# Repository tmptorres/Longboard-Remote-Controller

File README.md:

# Longboard-Remote-Controller

A remote controller board that uses an Arduino Nano and a 2.4GHz nRF24 WiFi module to send an analog input from a joystic (thumbstick). Power is provided by a 18650 Lithium-ion (Li-ion/Liion) battery.

## Product

## Top View

## Bottom View

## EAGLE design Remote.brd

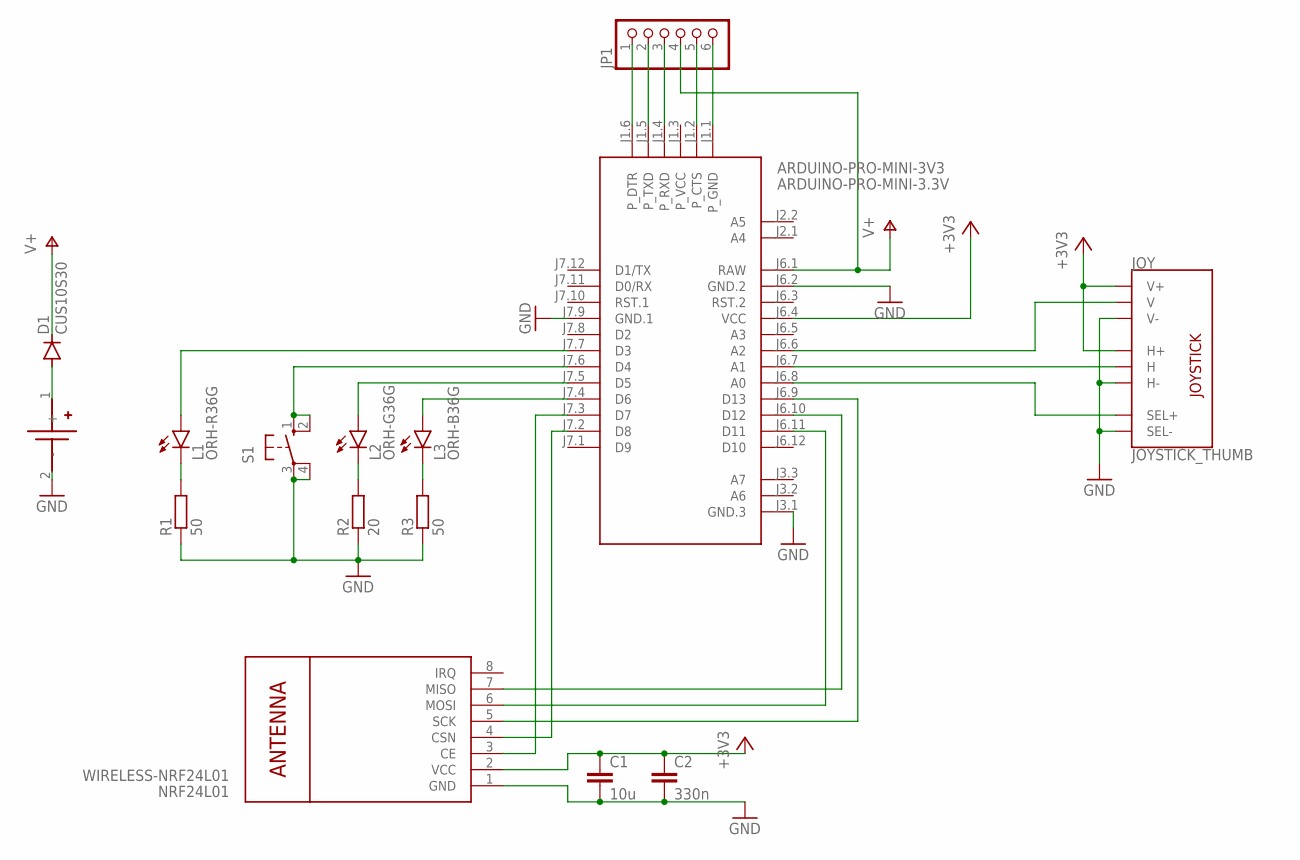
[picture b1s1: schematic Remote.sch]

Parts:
ARDUINO-PRO-MINI-3V3: ARDUINO-PRO-MINI-3.3V; ARDUINO-PRO-MINI
C1: 10u; C0805
C2: 330n; C0805
D1: CUS10S30; SOD323-W
JOY: JOYSTICK_THUMB; JOYSTICK
JP1: PINHD-1X6; 1X06
L1: ORH-R36G; CHIP-LED0603
L2: ORH-G36G; CHIP-LED0603
L3: ORH-B36G; CHIP-LED0603
NRF24L01: WIRELESS-NRF24L01
R1, R3: 50; R0603
R2: 20; R0603
S1: 10-XX; B3F-10XX
U$2: BLOSSOM-BLM-18650-1PCSNO-SCREWS; BLOSSOM-BLM-18650-1PCS-NO-SCREWS-SMALL-HOLES

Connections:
+3V3: ARDUINO-PRO-MINI-3V3.J6.4 (VCC), C1.1, C2.1, JOY.H1 (H+), JOY.V1 (V+), NRF24L01.2 (VCC)
GND: ARDUINO-PRO-MINI-3V3.J3.1 (GND.3), ARDUINO-PRO-MINI-3V3.J6.2 (GND.2), ARDUINO-PRO-MINI-3V3.J7.9 (GND.1), C1.2, C2.2, JOY.B2A (SEL-), JOY.H3 (H-), JOY.V3 (V-), NRF24L01.1 (GND), R1.1, R2.1, R3.1, S1.3, S1.4 (P1), U$2.2 (-)
unnamed: D1.A, U$2.1 (+)
unnamed: ARDUINO-PRO-MINI-3V3.J7.7 (D3), L1.A
unnamed: ARDUINO-PRO-MINI-3V3.J7.5 (D5), L2.A
unnamed: ARDUINO-PRO-MINI-3V3.J7.3 (D7), NRF24L01.3 (CE)
unnamed: ARDUINO-PRO-MINI-3V3.J7.2 (D8), NRF24L01.4 (CSN)
unnamed: ARDUINO-PRO-MINI-3V3.J6.9 (D13), NRF24L01.5 (SCK)
unnamed: ARDUINO-PRO-MINI-3V3.J6.11 (D11), NRF24L01.6 (MOSI)
unnamed: ARDUINO-PRO-MINI-3V3.J6.10 (D12), NRF24L01.7 (MISO)
unnamed: ARDUINO-PRO-MINI-3V3.J6.8 (A0), JOY.B1A (SEL+)
unnamed: ARDUINO-PRO-MINI-3V3.J6.7 (A1), JOY.H2 (H)
unnamed: ARDUINO-PRO-MINI-3V3.J6.6 (A2), JOY.V2 (V)
unnamed: ARDUINO-PRO-MINI-3V3.J7.4 (D6), L3.A
unnamed: L3.C, R3.2
unnamed: L2.C, R2.2
unnamed: L1.C, R1.2
unnamed: ARDUINO-PRO-MINI-3V3.J1.6 (P_DTR), JP1.1
unnamed: ARDUINO-PRO-MINI-3V3.J1.5 (P_TXD), JP1.2
unnamed: ARDUINO-PRO-MINI-3V3.J1.4 (P_RXD), JP1.3
unnamed: ARDUINO-PRO-MINI-3V3.J7.6 (D4), S1.1 (S), S1.2 (S1)
unnamed: ARDUINO-PRO-MINI-3V3.J1.2 (P_CTS), JP1.5
unnamed: ARDUINO-PRO-MINI-3V3.J1.1 (P_GND), JP1.6
V+: ARDUINO-PRO-MINI-3V3.J6.1 (RAW), D1.C, JP1.4

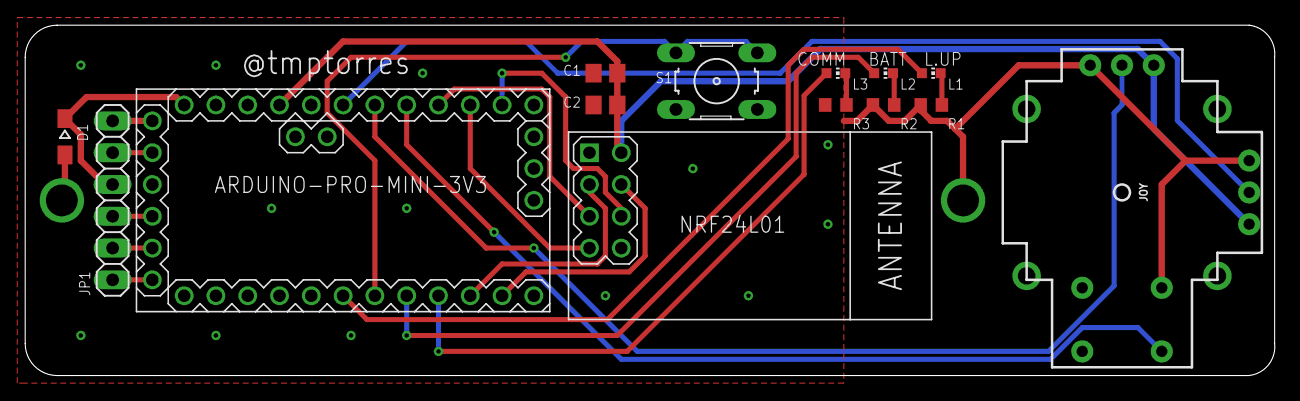
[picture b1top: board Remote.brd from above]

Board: 2 copper layers, 99.8 x 28.0 mm, 15 parts (1 on the bottom side), 24 nets.

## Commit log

2019-08-08 Added Remote PCB schematic and board design
2019-08-08 Changes to submodule. Modified 18650 battery holder
2019-08-11 GND trace width change. Updated silkscreen and created CAM files
2019-08-11 Added gitignore file
2019-08-11 Updated readme with board images
2021-01-18 Updated Readme.me and added finished product picture

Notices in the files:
parts and their libraries:
diy-modules: Released under the Creative Commons Attribution 4.0 International License: http://creativecommons.org/licenses/by/4.0
SparkFun-Switches: Licensing: Creative Commons ShareAlike 4.0 International - https://creativecommons.org/licenses/by-sa/4.0
